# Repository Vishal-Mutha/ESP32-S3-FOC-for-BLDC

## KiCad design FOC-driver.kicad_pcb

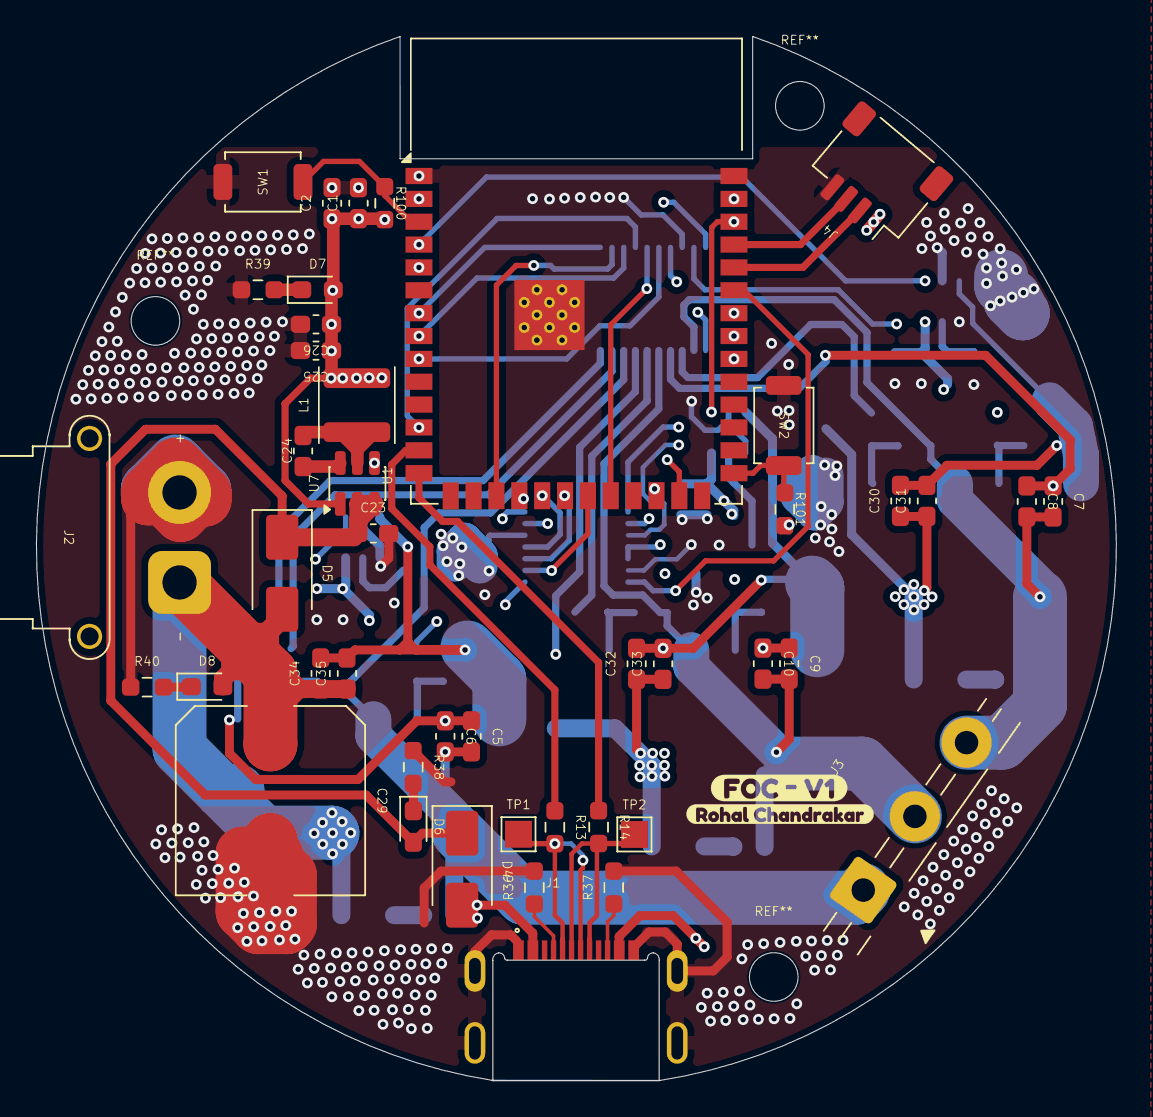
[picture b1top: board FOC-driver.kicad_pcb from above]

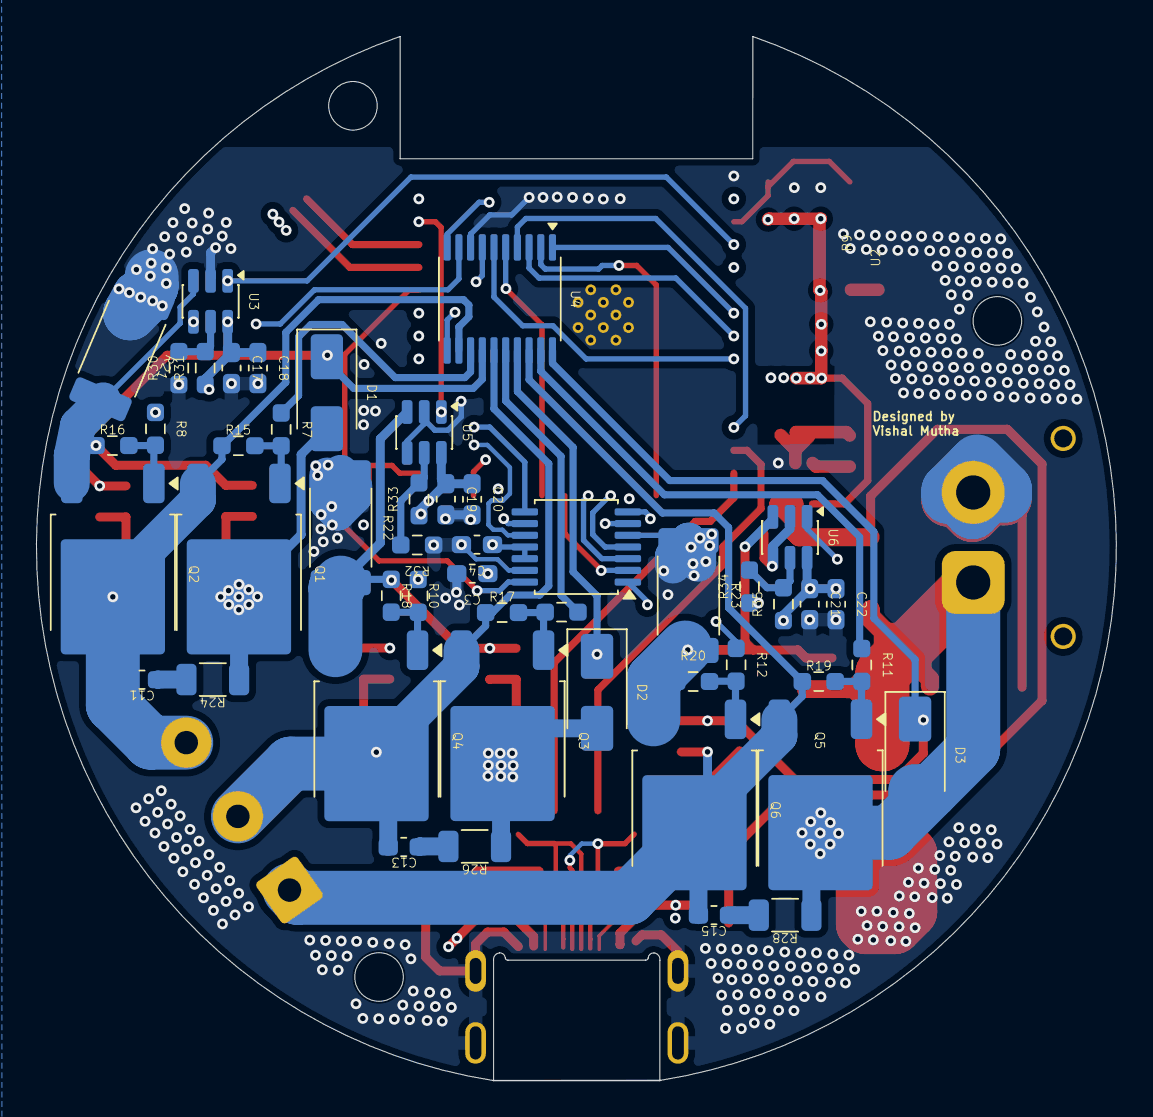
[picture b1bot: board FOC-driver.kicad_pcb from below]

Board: 4 copper layers, 60.0 x 58.0 mm, 95 parts (49 on the bottom side), 66 nets.

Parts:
C1, C3, C5, C7, C9, C17, C19, C21, C24, C30, C32, C34: 0.1uF; C_0603_1608Metric_Pad1.08x0.95mm_HandSolder
C2, C4, C6, C8, C10, C18, C20, C22, C31, C33, C35: 1uF; C_0603_1608Metric_Pad1.08x0.95mm_HandSolder
C11, C13, C15: 2.2nF; C_0603_1608Metric_Pad1.08x0.95mm_HandSolder
C23: 10uF; C_0603_1608Metric_Pad1.08x0.95mm_HandSolder
C25, C26: 22uF; C_0603_1608Metric_Pad1.08x0.95mm_HandSolder
C29: 470uF; C_Elec_10x10.2
D1, D2, D3, D4, D5: SS34; D_SMA
D6: RED; LED_0603_1608Metric_Pad1.05x0.95mm_HandSolder
D7: BLUE; LED_0603_1608Metric_Pad1.05x0.95mm_HandSolder
D8: GREEN; LED_0603_1608Metric_Pad1.05x0.95mm_HandSolder
J1: USB_C_Receptacle_USB2.0_16P; AMPHENOL_10155679-00031LF
J2: 12V XT60; AMASS_XT30PW-F_1x02_P2.50mm_Horizontal
J3: MOTOR PHASES; TerminalBlock_MaiXu_MX126-5.0-03P_1x03_P5.00mm
J4: S3_UART; JST_SH_SM04B-SRSS-TB_1x04-1MP_P1.00mm_Horizontal
L1: 3.9uH; L_APV_ANR4030
Q1, Q2, Q3, Q4, Q5, Q6: IRLR7843; TO-252-2
R7, R8, R9, R10, R11, R12: 10R; R_0603_1608Metric_Pad0.98x0.95mm_HandSolder
R13, R14: 22E; R_0603_1608Metric_Pad0.98x0.95mm_HandSolder
R15, R16, R17, R18, R19, R20, R30, R31, R32, R33, R34, R35, R40, R100, R101: 10k; R_0603_1608Metric_Pad0.98x0.95mm_HandSolder
R21, R22, R23: 5mR; R_2512_6332Metric_Pad1.40x3.35mm_HandSolder
R24, R26, R28: 10R; R_1206_3216Metric
R36, R37, R38: 5.1k; R_0603_1608Metric_Pad0.98x0.95mm_HandSolder
R39: 3k; R_0603_1608Metric_Pad0.98x0.95mm_HandSolder
SW1, SW2: tactile_push; SW_SPST_TS-1088-xR025
TP1: D-; TestPoint_Pad_1.5x1.5mm
TP2: D+; TestPoint_Pad_1.5x1.5mm
U1: ESP32-S3-WROOM-1
U2: AS5047D; TSSOP-14_4.4x5mm_P0.65mm
U3, U5, U6: INA181; SOT-23-6
U4: FD6288; TSSOP-20_4.4x6.5mm_P0.65mm
U7: AP63203WU; TSOT-23-6
kibuzzard-6A9D1F00: G***; kibuzzard-6A9D1F00
kibuzzard-6A9D1F23: G***; kibuzzard-6A9D1F23

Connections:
/3V3: C1.1, C2.1, C3.1, C4.1, C17.1, C18.1, C19.1, C20.1, C21.1, C22.1, C25.1, C26.1, D7.2 (A), J4.1, L1.2, R31.1, R33.1, R35.1, R100.2, R101.2, U1.2 (3V3), U2.11 (VDD), U2.12 (VDD3V3), U3.6 (V+), U5.6 (V+), U6.6 (V+), U7.1 (FB)
/5V: C23.1, D4.1 (K), D5.1 (K), D6.2 (A), U7.2 (EN), U7.3 (IN)
/12V: C29.1, C30.1, C31.1, C32.1, C33.1, C34.1, C35.1, D1.2 (A), D2.2 (A), D3.2 (A), D5.2 (A), D8.2 (A), J2.1, Q1.2 (D), Q3.2 (D), Q5.2 (D), R24.2, R26.2, R28.2, U4.7 (VCC)
/A: U1.24 (IO47), U2.7 (A)
/B: U1.25 (IO48), U2.6 (B)
/CS: U1.18 (IO10), U2.1 (~CS)
/D+: J1.A6 (D+), J1.B6 (D+), R14.2, TP2.1 (1_1)
/D-: J1.A7 (D-), J1.B7 (D-), R13.2, TP1.1 (1_1)
/HIN_1: U1.7 (IO7), U4.1 (HIN1)
/HIN_2: U1.17 (IO9), U4.2 (HIN2)
/HIN_3: U1.8 (IO15), U4.3 (HIN3)
/HO1: R11.1, U4.19 (HO1)
/HO2: R9.1, U4.16 (HO2)
/HO3: R7.1, U4.13 (HO3)
/I: U1.35 (IO42), U2.14 (I/PWM)
/I+1: C34.2, C35.2, Q6.3 (S), R20.1, R23.2, U6.3 (+)
/I+2: C32.2, C33.2, Q4.3 (S), R18.1, R22.2, U5.3 (+)
/I+3: C30.2, C31.2, Q2.3 (S), R16.1, R21.2, U3.3 (+)
/I_1: U1.39 (IO1), U6.1
/I_2: U1.38 (IO2), U5.1
/I_3: U1.4 (IO4), U3.1
/LIN_1: U1.12 (IO8), U4.4 (LIN1)
/LIN_2: U1.22 (IO14), U4.5 (LIN2)
/LIN_3: U1.9 (IO16), U4.6 (LIN3)
/LO1: R12.1, U4.11 (LO1)
/LO2: R10.1, U4.10 (LO2)
/LO3: R8.1, U4.9 (LO3)
/MISO: U1.20 (IO12), U2.3 (MISO)
/MOSI: U1.19 (IO11), U2.4 (MOSI)
/S3_RX: J4.2, U1.36 (RXD0)
/S3_TX: J4.3, U1.37 (TXD0)
/SCLK: U1.21 (IO13), U2.2 (CLK)
/U: U1.32 (IO39), U2.10 (U)
/V: U1.33 (IO40), U2.9 (V)
/VB1: C5.1, C6.1, D3.1 (K), U4.20 (VB1)
/VB2: C9.1, C10.1, D2.1 (K), U4.17 (VB2)
/VB3: C7.1, C8.1, D1.1 (K), U4.14 (VB3)
/VS1: C5.2, C6.2, C15.2, J3.1, Q5.3 (S), Q6.2 (D), R19.1, U4.18 (VS1)
/VS2: C9.2, C10.2, C13.2, J3.2, Q3.3 (S), Q4.2 (D), R17.1, U4.15 (VS2)
/VS3: C7.2, C8.2, C11.2, J3.3, Q1.3 (S), Q2.2 (D), R15.1, U4.12 (VS3)
/W: U1.34 (IO41), U2.8 (W/PWM)
GND: C1.2, C2.2, C3.2, C4.2, C17.2, C18.2, C19.2, C20.2, C21.2, C22.2, C23.2, C25.2, C26.2, C29.2, J1.A1 (GND), J1.B1 (GND), J1.SH (SHIELD), J2.2, J4.4, R21.1, R22.1, R23.1, R30.1, R32.1, R34.1, R36.2, R37.2, R38.1, R39.1, R40.1, SW1.1, SW2.1, U1.1 (GND), U1.40 (GND), U1.41 (GND), U2.5 (TST), U2.13 (GND), U3.2 (GND), U3.4 (-), U4.8 (COM), U5.2 (GND), U5.4 (-), U6.2 (GND), U6.4 (-), U7.4 (GND)
unnamed: C11.1, R24.1
unnamed: C13.1, R26.1
unnamed: C15.1, R28.1
unnamed: D4.2 (A), J1.A4 (VBUS), J1.B4 (VBUS)
unnamed: D6.1 (K), R38.2
unnamed: D7.1 (K), R39.2
unnamed: D8.1 (K), R40.2
unnamed: J1.A5 (CC1), R36.1
unnamed: J1.B5 (CC2), R37.1
unnamed: Q1.1 (G), R7.2, R15.2
unnamed: Q2.1 (G), R8.2, R16.2
unnamed: Q3.1 (G), R9.2, R17.2
unnamed: Q4.1 (G), R10.2, R18.2
unnamed: Q5.1 (G), R11.2, R19.2
unnamed: Q6.1 (G), R12.2, R20.2
unnamed: R100.1, SW1.2, U1.3 (EN)
unnamed: R101.1, SW2.2, U1.27 (IO0)
unnamed: R14.1, U1.14 (USB_D+)
unnamed: R13.1, U1.13 (USB_D-)
unnamed: R30.2, R31.2, U3.5 (REF)
unnamed: R32.2, R33.2, U5.5 (REF)
unnamed: R34.2, R35.2, U6.5 (REF)
unnamed: C24.2, U7.6 (BST)
unnamed: C24.1, L1.1, U7.5 (SW)
